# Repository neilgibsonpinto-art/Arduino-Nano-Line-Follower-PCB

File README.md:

# Arduino Nano PID Line Follower PCB

A custom, competition-ready **autonomous line follower robot mainboard** powered by the **Arduino Nano** and **Toshiba TB6612FNG** dual motor driver. Designed for high-speed robotics competitions, STEM educational kits, and embedded systems learning.

The board features a modular 8-channel analog IR sensor interface, hardware push buttons for calibration and run initiation, power management with reverse polarity protection, and high-current traces for micro metal gearmotors.

---

## 📸 Board Previews

### PCB Layout (Top & Bottom)
<p align="center">
  
  &nbsp;
  
</p>

### Schematic Diagram
<p align="center">
  
  <br>
  <em>(Click to open or download the high-resolution <a href="Docs/Schematic.pdf">Schematic PDF</a>)</em>
</p>

---

## ⚡ Key Specifications

| Parameter | Specification | Details |
| :--- | :--- | :--- |
| **Microcontroller** | Arduino Nano (ATmega328P) | 16 MHz, 32 KB Flash, 2 KB SRAM |
| **Motor Driver** | TB6612FNG Dual H-Bridge Module | 1.2A continuous / 3.2A peak per channel |
| **Sensor Interface** | 10-Pin JST-XH Header | Supports 8 analog IR sensors (A0–A7) + 5V/GND |
| **Operating Voltage** | 7.4V – 8.4V (2S LiPo Pack) | Reverse-polarity protected with SS34 Schottky diode |
| **Logic Regulation** | LM7805 TO-220 Linear Regulator | With aluminum heatsink bracket |
| **Drive Architecture** | 2-Wheel Differential Drive | 2 × 2-Pin JST motor connectors (L1/L2, R1/R2) |
| **User Controls** | 2 × Tactile Push Buttons | Dedicated `START` and `CALIBRATION` inputs |
| **Status Feedback** | 5mm Through-Hole LED | User-programmable indicator on D12 |
| **Power Switch** | SPDT Miniature Slide Switch | Direct mechanical battery disconnect |
| **Board Dimensions** | 70.0 mm × 50.0 mm | Standard 1.6 mm FR-4, 4 × M3 corner mounting holes |

---

## 🗺️ Pinout & Hardware Mapping

### Arduino Nano Pin Assignments

| Arduino Nano Pin | Net Name | Connected To | Function / Description |
| :---: | :---: | :---: | :--- |
| **D2** | `P1` | `START_1` Button | Run / Trigger initiation button (Active LOW) |
| **D3** | `calib` | `CALIBRATION_1` Button | Sensor calibration routine trigger (Active LOW) |
| **D4** | `STBY` | TB6612FNG Pin 13 (`STBY`) | Motor driver standby enable (Active HIGH) |
| **D5** | `PWMA` | TB6612FNG Pin 16 (`PWMA`) | Left motor PWM speed control (Timer0) |
| **D6** | `PWMB` | TB6612FNG Pin 10 (`PWMB`) | Right motor PWM speed control (Timer0) |
| **D7** | `AIN2` | TB6612FNG Pin 15 (`AI2`) | Left motor direction input 2 |
| **D8** | `AIN1` | TB6612FNG Pin 14 (`AI1`) | Left motor direction input 1 |
| **D9** | `BIN1` | TB6612FNG Pin 12 (`BI1`) | Right motor direction input 1 |
| **D10** | `BIN2` | TB6612FNG Pin 11 (`BI2`) | Right motor direction input 2 |
| **D12** | `led` | Status LED (`D2`) | User diagnostic indicator |
| **A0 – A7** | `A0` – `A7` | Sensor Header `J1` (Pins 2–9) | 8-Channel Analog IR sensor readings |
| **5V** | `+5V` | LM7805 Output / VCC Rail | System logic supply |
| **GND** | `GND` | Common Ground Plane | Star ground return |

---

## 📦 Bill of Materials (BOM)

| Ref Des | Qty | Component Value | Package / Footprint | Procurement Link |
| :--- | :---: | :--- | :--- | :--- |
| **U1** | 1 | Arduino Nano V3.0 (CH340/FTDI) | Socket / Module Footprint | [Robu.in Link](https://robu.in/product/arduino-nano-board-r3-ch340-chip-with-usb-cable-solderedarduino-nano-r3-usb-cable/) |
| **U2** | 1 | TB6612FNG Motor Driver Module | SparkFun ROB-14450 Compatible | [Robu.in Link](https://robu.in/product/motor-driver-tb6612fng-module-performance-ultra-small-volume-3-pi-matching-performance-ultra-l298n/) |
| **U3** | 1 | LM7805 Linear Regulator (5V, 1.5A) | TO-220-3 Vertical | [Robu.in Link](https://robu.in/product/l7805cv-stmicroelectronics-linear-voltage-regulator-7805-fixed-positive-10v-to-35v-in-5v-and-1-5a-out-to-220-3/) |
| **D1** | 1 | SS34 Schottky Barrier Diode (3A, 40V) | SMD DO-214AC (SMA) | [Robu.in Link](https://robu.in/product/ss34-slkor-40v-500mv3a-3a-smado-214ac-schottky-diodes-rohs/) |
| **D2** | 1 | Red LED (5mm DIP) | LED_D5.0mm Through-Hole | [Robu.in Link](https://robu.in/product/5mm-red-dip-led-pack-of-50/) |
| **C1, C2** | 2 | 10 µF 25V Electrolytic Capacitor | Radial D5.0mm, P2.00mm | [Robu.in Link](https://robu.in/product/10-uf-25v-through-hole-electrolytic-capacitor-pack-of-40/) |
| **SW1** | 1 | SPDT Miniature Slide Switch | SW_MINI-SPDT | [Robu.in Link](https://robu.in/product/1-month-warranty-255/) |
| **START1, CALIBRATION1** | 2 | 6x6 mm Tactile Push Button | SW_PUSH_6mm Through-Hole | [Robu.in Link](https://robu.in/product/tsd001a06018a-bzcn-6mm-6mm-50ma-round-button-direct-insert-6mm-180gf-12v-plugin-tactile-switches-rohs/) |
| **J1** | 1 | 10-Pin JST-XH Straight Male Header | JST_B10B-XH-A 2.5mm Pitch | [Robu.in Link](https://robu.in/product/b10b-xh-amlfsn-jst-1x10p-10p-xh-tin-10-25%E2%84%8385%E2%84%83-3a-1-2-5mm-brass-direct-insert-pluginp2-5mm-wire-to-board-connector-rohs/) |
| **J2** | 1 | 2-Pin Screw Terminal Block (5.0mm) | XY306A-5.0 2P Blue | [Robu.in Link](https://robu.in/product/xy306a-5-0-xinya-2-pin-screw-terminal-blockblue/) |
| **J3, J4** | 2 | 2-Pin JST-XH/PH Motor Connectors | S2B-PH-K-S / JST 2-Pin 2.54mm | [Robu.in Link](https://robu.in/product/2-pin-jst-xh-2-54mm-pitch-plug-and-socket-with-cable-10-pcs/) |
| **Heatsink** | 1 | Aluminum TO-220 Heatsink | TO220-718 with Screw | [Robu.in Link](https://robu.in/product/to220-718-aluminum-heatsink-for-transistor-pack-of-5/) |

---

## 🧠 PID Line Following Algorithm

The robot uses a **Weighted Average Centroid** algorithm to calculate the position of the line relative to the center of the 8-sensor array:

$$\text{Error} = \frac{\sum_{i=0}^{7} \text{SensorValue}_i \times \text{Weight}_i}{\sum_{i=0}^{7} \text{SensorValue}_i}$$

Where $\text{Weight} = \{-3500, -2500, -1500, -500, 500, 1500, 2500, 3500\}$.

### PID Steering Correction
$$\text{Correction} = (K_p \times \text{Error}) + \left(K_i \times \sum \text{Error}\right) + (K_d \times \Delta\text{Error})$$

* **Left Motor Speed:** $V_{\text{left}} = V_{\text{base}} + \text{Correction}$
* **Right Motor Speed:** $V_{\text{right}} = V_{\text{base}} - \text{Correction}$

If the line is momentarily lost (all sensors off track), the algorithm retains the last known error sign to continue turning back onto the track.

The complete code is located in [`Firmware/LineFollower/LineFollower.ino`](Firmware/LineFollower/LineFollower.ino).

---

## 🛠️ Hardware Design & Assembly Notes

> [!IMPORTANT]
> **Rev 1.0 Bring-Up Instructions:**
> 1. **Arduino Nano 5V Power Pin:** In Rev 1.0, the 5V regulated output is wired to Nano Pin 30 (`VIN`). For optimal operation and to bypass the Nano's onboard regulator dropout, bridge Nano Pin 27 (`5V`) to the board's `+5V` rail.
> 2. **LED Series Resistor:** When assembling Rev 1.0, place a **330 Ω** resistor in series with LED `D2` to protect GPIO pin D12 from overcurrent.
> 3. **Input Voltage Recommendation:** The LM7805 has a ~2.0V dropout voltage. When running on a 2S LiPo (7.4V nominal), consider using an **LM2940CT-5.0** low-dropout regulator (0.5V dropout, pin-compatible TO-220) for full discharge headroom down to 6.0V.
> 4. **Decoupling Capacitors:** In addition to the electrolytic capacitors, solder a 100 nF ceramic capacitor across the motor driver VM-GND to absorb high-frequency PWM switching transients.

---

## 🏭 Manufacturing & Fabrication Files

The board is designed for standard low-cost PCB fabrication (JLCPCB, PCBWay, etc.):

* **Layers:** 2-Layer Board
* **Dimensions:** 70.0 mm × 50.0 mm
* **PCB Thickness:** 1.6 mm
* **Copper Weight:** 1 oz (35 µm)
* **Surface Finish:** HASL (or Lead-free HASL / ENIG)
* **Minimum Trace / Space:** 0.25 mm / 0.25 mm (Power traces 1.0 mm)
* **Gerber Archive:** Ready-to-order Gerber ZIP is available at [`Gerber/lineFollow_Gerbers.zip`](Gerber/lineFollow_Gerbers.zip).

---

## 📂 Repository Structure

```
Arduino-Nano-Line-Follower-PCB/
│
├── Firmware/
│   └── LineFollower/
│       └── LineFollower.ino         # Arduino PID line follower firmware
│
├── Gerber/
│   ├── lineFollow_Gerbers.zip       # Complete fabrication archive (JLCPCB / PCBWay ready)
│   ├── lineFollow.drl               # Excellon drill file
│   ├── lineFollow-F_Cu.gtl          # Top copper layer
│   ├── lineFollow-B_Cu.gbl          # Bottom copper layer
│   ├── lineFollow-F_Silkscreen.gto  # Top silkscreen
│   └── ...                          # Solder masks, paste, edge cuts
│
├── Images/
│   ├── PCB_Top.svg                  # Vector render of top copper and silkscreen
│   ├── PCB_Bottom.svg               # Vector render of bottom copper and ground fill
│   └── Schematic.svg                # Vector circuit schematic diagram
│
├── Docs/
│   ├── Schematic.pdf                # Full printable A4 schematic sheet
│   └── BOM.csv                      # Bill of materials with part numbers & links
│
├── lineFollow.kicad_sch             # KiCad 10 schematic file
├── lineFollow.kicad_pcb             # KiCad 10 board layout
├── lineFollow.kicad_pro             # KiCad project file
├── LINE FOLLOWER PCB.step           # 3D mechanical CAD model (STEP)
├── lineFollow.csv                   # Component procurement links
├── .gitignore                       # Git ignore for EDA cache and backups
└── README.md                        # Project documentation
```

---

## 👨‍💻 Author

**Neil Gibson Pinto**  
*Electronics & Communication Engineering*  
*Specialized in Embedded Systems, Robotics, and Custom Hardware Design.*

---

## 📄 License

This hardware design and source code are released under the [MIT License](LICENSE).
Feel free to use, modify, and build upon this design for academic, competition, and commercial projects.

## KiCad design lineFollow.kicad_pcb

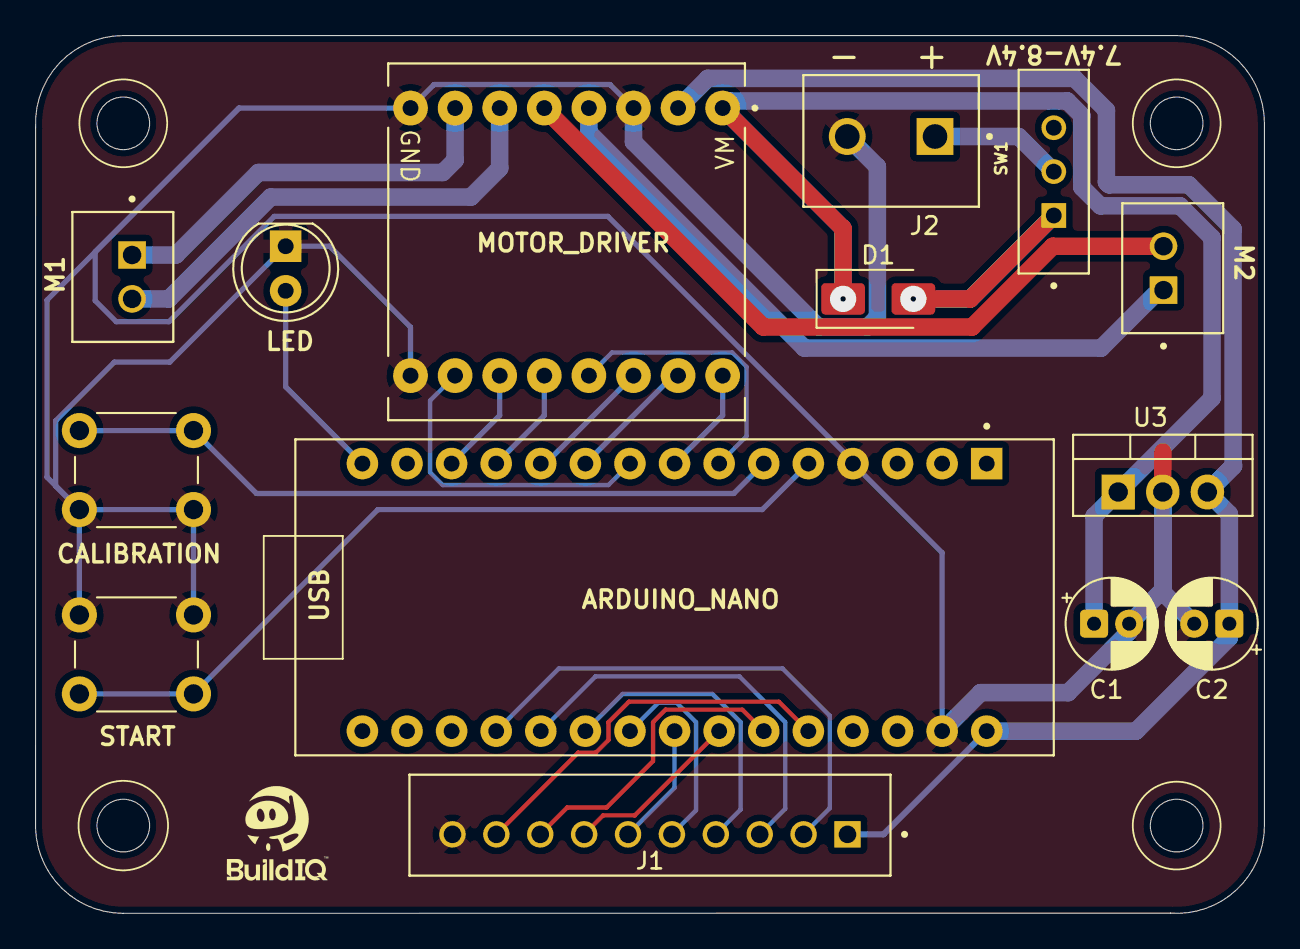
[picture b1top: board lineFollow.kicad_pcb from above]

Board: 2 copper layers, 70.0 x 50.0 mm, 14 parts (0 on the bottom side), 27 nets.

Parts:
C1, C2: 10µF; CP_Radial_D5.0mm_P2.00mm
CALIBRATION_1: SW_Push; SW_PUSH_6mm
D1: D_Schottky; D_SMA
D2: LED; LED_D5.0mm
J1: Conn_01x10_Pin; JST_B10B-XH-A_LF__SN_
J2: Conn_01x02; screw_conn
J3, J4: S2B-PH-K-S_LF__SN_; jst_2pin
START_1: SW_Push; SW_PUSH_6mm
SW1: SW_SPDT; SW_MINI-SPDT-SW
U1: ARDUINO_NANO; MODULE_ARDUINO_NANO
U2: ROB-14450; MODULE_ROB-14450
U3: LM7805_TO220; TO-220-3_Vertical

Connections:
+5V: C2.1, J1.1, U1.30 (VIN), U2.2 (VCC), U3.3 (VO)
A0: J1.2, U1.19 (A0)
A1: J1.3, U1.20 (A1)
A2: J1.4, U1.21 (A2)
A3: J1.5, U1.22 (A3)
A4: J1.6, U1.23 (A4)
A5: J1.7, U1.24 (A5)
A6: J1.8, U1.25 (A6)
A7: J1.9, U1.26 (A7)
AIN1: U1.11 (D8), U2.14 (AI1)
AIN2: U1.10 (D7), U2.15 (AI2)
BIN1: U1.12 (D9), U2.12 (BI1)
BIN2: U1.13 (D10), U2.11 (BI2)
GND: C1.2, C2.2, CALIBRATION_1.1, D2.1 (K), J1.10, J2.2, START_1.1, U1.4 (GND_4), U1.29 (GND_29), U2.3 (GND), U2.8 (GND), U2.9 (GND), U3.2 (GND)
L1: J3.1, U2.4 (A01)
L2: J3.2, U2.5 (A02)
unnamed: D1.2 (A), SW1.1 (A)
unnamed: J2.1, SW1.2 (B)
P1: START_1.2, U1.5 (D2)
PWMA: U1.8 (D5), U2.16 (PWMA)
PWMB: U1.9 (D6), U2.10 (PWMB)
R1: J4.1, U2.7 (B01)
R2: J4.2, U2.6 (B02)
STBY: U1.7 (D4), U2.13 (STBY)
VIN: C1.1, D1.1 (K), U2.1 (VM), U3.1 (VI)
calib: CALIBRATION_1.2, U1.6 (D3)
led: D2.2 (A), U1.15 (D12/MISO)

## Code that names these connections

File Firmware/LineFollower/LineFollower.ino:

/*
 ==============================================================================
  Project: Arduino Nano PID Line Follower Robot
  Author:  Neil Gibson Pinto
  Hardware: Custom Arduino Nano Line Follower PCB
            - Controller: Arduino Nano (ATmega328P)
            - Motor Driver: SparkFun TB6612FNG Module (ROB-14450)
            - Sensor Array: 8-Channel Analog IR Sensor Bar (A0 - A7)
            - Indicator: Status LED (D12)
            - Control: Start Button (D2), Calibration Button (D3)
 ==============================================================================
*/

// ------------ Sensor Configuration ------------
#define NUM_SENSORS 8
const int sensorPins[NUM_SENSORS] = {A0, A1, A2, A3, A4, A5, A6, A7};
int sensorValue[NUM_SENSORS];

// ------------ TB6612FNG Motor Driver Pins ------------
#define STBY 4    // Standby enable pin (Active HIGH)
#define PWMA 5    // Left Motor Speed (PWM)
#define AIN2 7    // Left Motor Direction 2
#define AIN1 8    // Left Motor Direction 1

#define PWMB 6    // Right Motor Speed (PWM)
#define BIN1 9    // Right Motor Direction 1
#define BIN2 10   // Right Motor Direction 2

// ------------ User Interface Pins ------------
#define BTN_START 2       // Start / Run Button (Active LOW)
#define BTN_CALIBRATE 3   // Sensor Calibration Button (Active LOW)
#define LED_STATUS 12     // Status LED Indicator

// ------------ PID Controller Parameters ------------
float Kp = 0.25;
float Ki = 0.00;
float Kd = 3.50;

float error = 0;
float previousError = 0;
float integral = 0;
float derivative = 0;
float correction = 0;

int baseSpeed = 170;
int maxSpeed = 255;

// Sensor position weights across the array
const int weights[8] = {-3500, -2500, -1500, -500, 500, 1500, 2500, 3500};

void setup()
{
  // Motor control pins
  pinMode(STBY, OUTPUT);
  pinMode(AIN1, OUTPUT);
  pinMode(AIN2, OUTPUT);
  pinMode(BIN1, OUTPUT);
  pinMode(BIN2, OUTPUT);

  // Push button inputs with internal pull-up resistors
  pinMode(BTN_START, INPUT_PULLUP);
  pinMode(BTN_CALIBRATE, INPUT_PULLUP);

  // Status indicator LED
  pinMode(LED_STATUS, OUTPUT);
  digitalWrite(LED_STATUS, LOW);

  // Enable motor driver
  digitalWrite(STBY, HIGH);

  Serial.begin(115200);

  // Optional: Wait for START button press before running
  // while (digitalRead(BTN_START) == HIGH) { delay(10); }
  // digitalWrite(LED_STATUS, HIGH);
}

void loop()
{
  readSensors();

  error = calculateError();

  integral += error;
  derivative = error - previousError;

  correction = (Kp * error) + (Ki * integral) + (Kd * derivative);

  previousError = error;

  int leftSpeed = baseSpeed + correction;
  int rightSpeed = baseSpeed - correction;

  leftSpeed = constrain(leftSpeed, -255, 255);
  rightSpeed = constrain(rightSpeed, -255, 255);

  setMotor(leftSpeed, rightSpeed);
}

// ----------------------------------------------------------------------------
// Read Analog Values from all 8 Sensors
// ----------------------------------------------------------------------------
void readSensors()
{
  for (int i = 0; i < NUM_SENSORS; i++)
  {
    sensorValue[i] = analogRead(sensorPins[i]);
  }
}

// ----------------------------------------------------------------------------
// Calculate Line Position Error using Weighted Average
// ----------------------------------------------------------------------------
float calculateError()
{
  long weightedSum = 0;
  long total = 0;

  for (int i = 0; i < NUM_SENSORS; i++)
  {
    int value = 1023 - sensorValue[i];
    if (value < 0) value = 0;

    weightedSum += (long)value * weights[i];
    total += value;
  }

  // If line is lost, hold the last turn direction
  if (total == 0)
  {
    if (previousError > 0)
      return 3500;
    else
      return -3500;
  }

  return (float)weightedSum / total;
}

// ----------------------------------------------------------------------------
// Differential Drive Motor Output
// ----------------------------------------------------------------------------
void setMotor(int left, int right)
{
  // Left Motor Control
  if (left >= 0)
  {
    digitalWrite(AIN1, HIGH);
    digitalWrite(AIN2, LOW);
  }
  else
  {
    digitalWrite(AIN1, LOW);
    digitalWrite(AIN2, HIGH);
    left = -left;
  }

  // Right Motor Control
  if (right >= 0)
  {
    digitalWrite(BIN1, HIGH);
    digitalWrite(BIN2, LOW);
  }
  else
  {
    digitalWrite(BIN1, LOW);
    digitalWrite(BIN2, HIGH);
    right = -right;
  }

  left = constrain(left, 0, maxSpeed);
  right = constrain(right, 0, maxSpeed);

  analogWrite(PWMA, left);
  analogWrite(PWMB, right);
}

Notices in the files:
README.md:
License: MIT
